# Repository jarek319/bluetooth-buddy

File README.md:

# bluetooth-buddy
Easily get debug info from your projects using a smartphone

Bluetooth Buddy was an idea I had to easily add a standard serial port using a simple headphone jack that I would connect a dongle to that would broadcast serial messages that it received over Bluetooth.

This is that dongle. Completely untested.

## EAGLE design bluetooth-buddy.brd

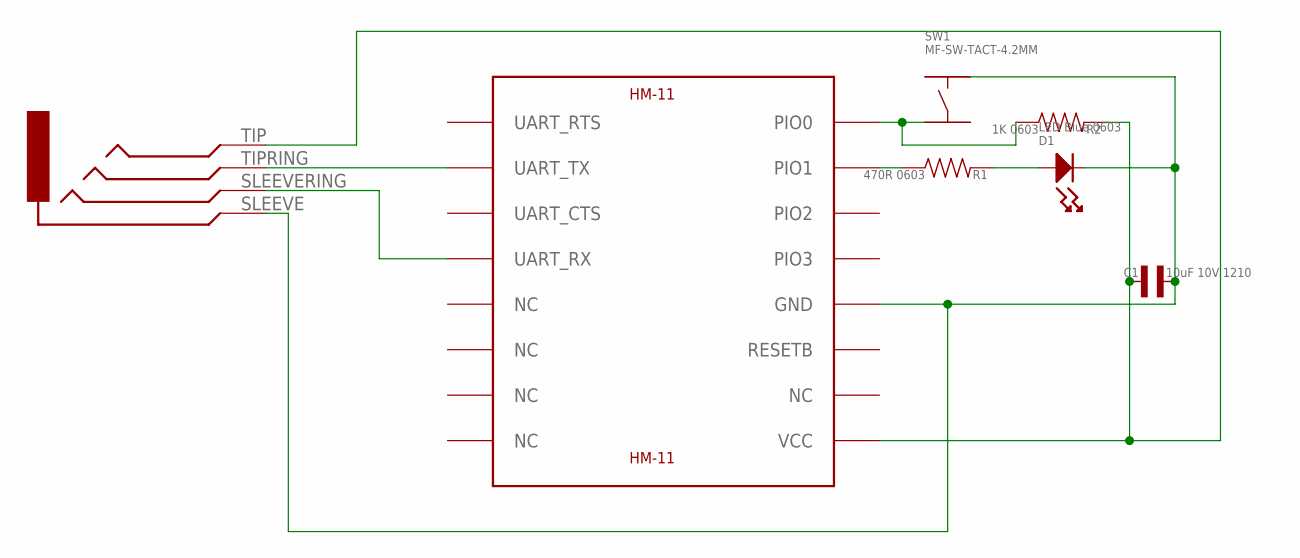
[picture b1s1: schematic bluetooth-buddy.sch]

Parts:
C1: 10uF 10V 1210; C1210
D1: LED Blue 0603; LED0603
J1: 54-00035
R1: 470R 0603; R0603
R2: 1K 0603; R0603
SW1: MF-SW-TACT-4.2MM; TACT4.2MM
U$1: HM-11

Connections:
GND: C1.P$1, D1.CATHODE, J1.SLEEVE (S), SW1.P$2, U$1.GND
unnamed: J1.TIPRING (RT), U$1.UART_TX
unnamed: J1.SLEEVERING (RS), U$1.UART_RX
unnamed: R1.P$1, U$1.PIO1
unnamed: R2.P$1, SW1.P$3, U$1.PIO0
unnamed: D1.ANODE, R1.P$2
unnamed: C1.P$2, J1.TIP (T), R2.P$2, U$1.VCC

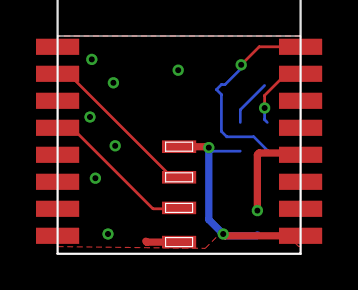
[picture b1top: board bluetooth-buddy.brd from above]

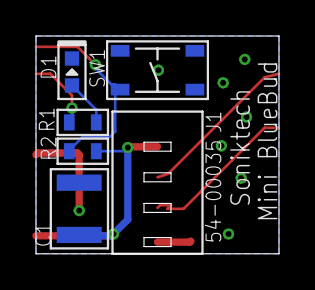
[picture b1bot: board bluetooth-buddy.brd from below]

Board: 2 copper layers, 13.5 x 12.1 mm, 7 parts (6 on the bottom side), 7 nets.

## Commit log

2018-07-04 design untested
